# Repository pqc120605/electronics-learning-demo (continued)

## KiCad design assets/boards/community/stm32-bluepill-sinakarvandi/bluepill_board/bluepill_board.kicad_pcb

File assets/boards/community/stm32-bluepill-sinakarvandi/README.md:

# PCB Designs

My random PCB designs using [KiCad](https://www.kicad.org/).

- **Blue Pill Board**

  Custom PCB design for STM32 "Blue Pill" development board.

- **ESP32-S3 Board**

  Schematic and layout for ESP32-S3-based design.

- **ESP32 WROOM Board**

  PCB based on ESP32-WROOM module.

- **LED Blinker**

  Simple circuit for testing LEDs and basic PCB workflow.

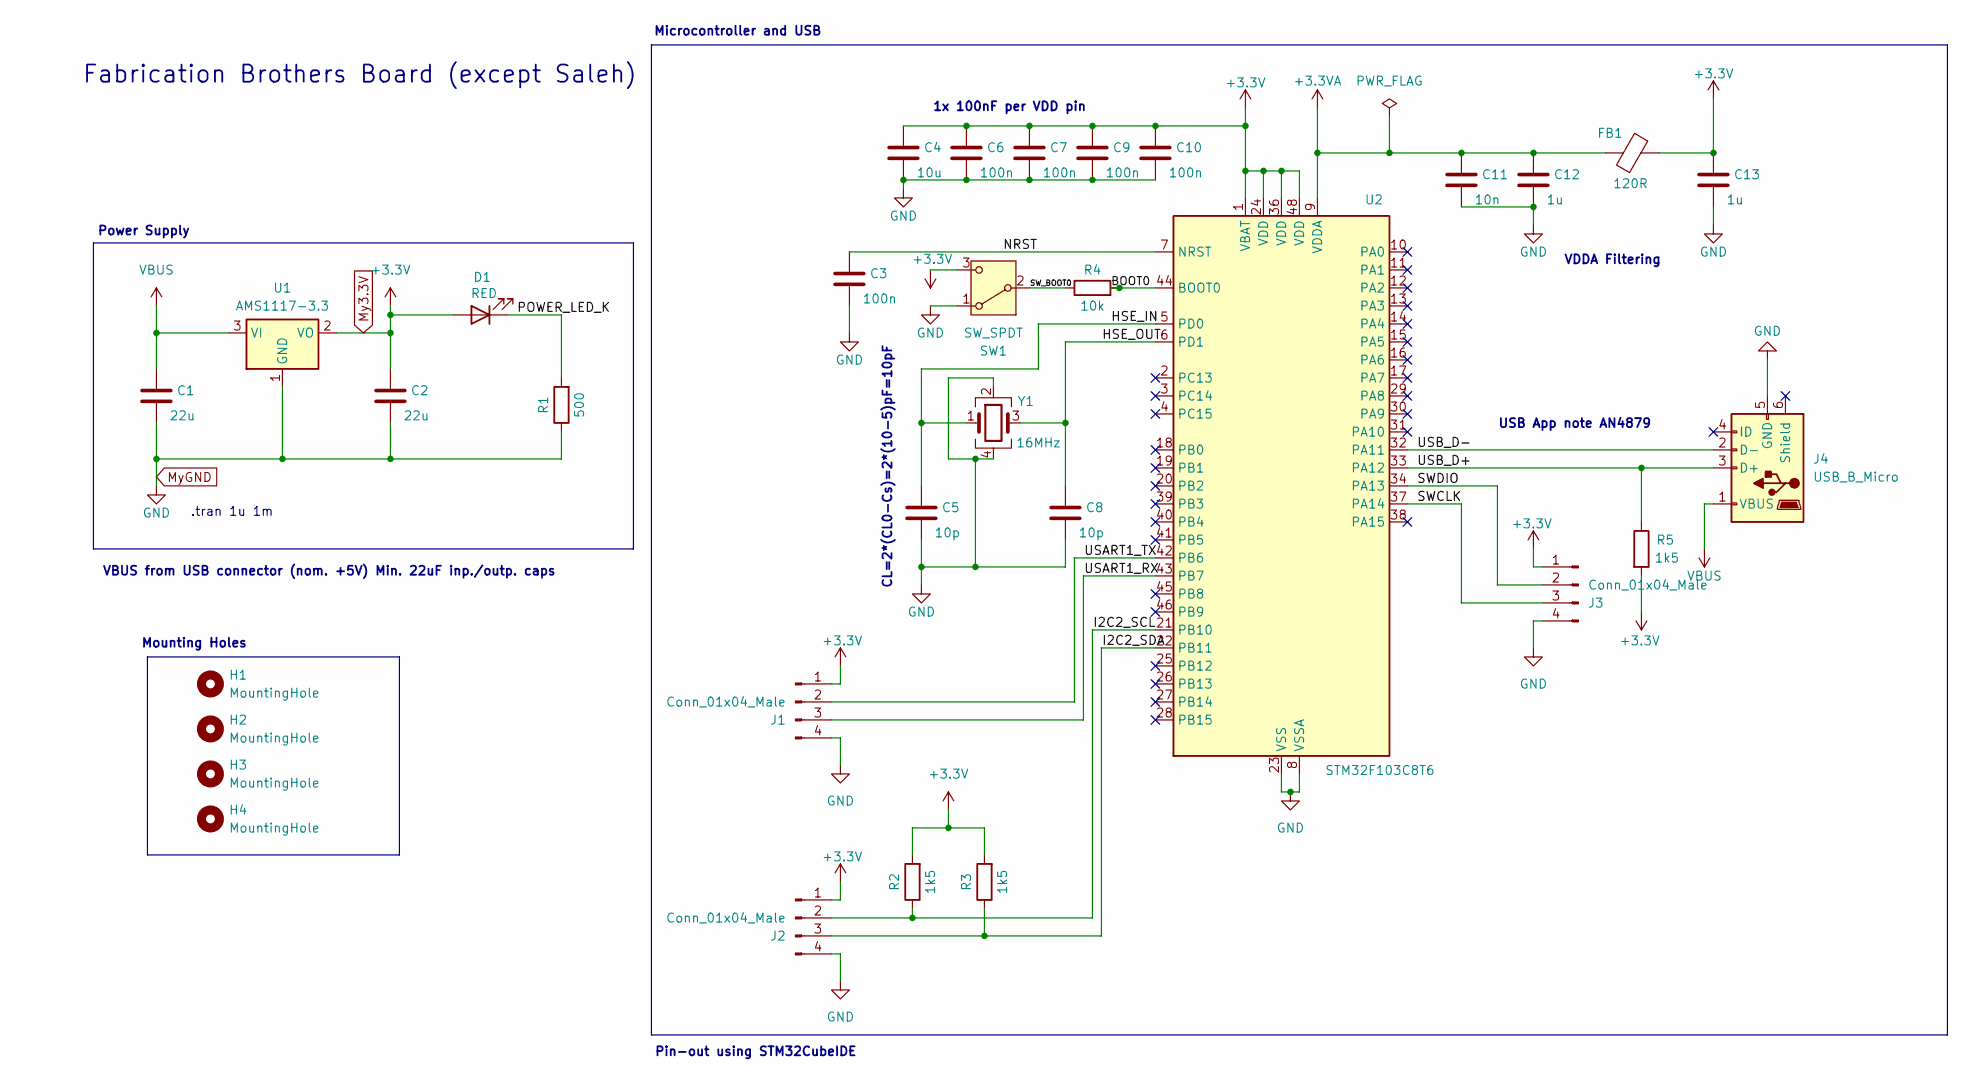
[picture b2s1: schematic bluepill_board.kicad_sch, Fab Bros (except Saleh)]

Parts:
C1, C2: 22u; C_0805_2012Metric; LCSC C296720
C3, C6, C7, C9, C10: 100n; C_0402_1005Metric; LCSC C1525
C4: 10u; C_0603_1608Metric; LCSC C19702
C5, C8: 10p; C_0402_1005Metric; LCSC C32949
C11: 10n; C_0402_1005Metric; LCSC C15195
C12, C13: 1u; C_0402_1005Metric; LCSC C29266
D1: RED; LED_0603_1608Metric; LCSC C7371906
FB1: 120R; L_0603_1608Metric; LCSC C14709
H1, H2, H3, H4: MountingHole; MountingHole_2.2mm_M2
J1, J2, J3: Conn_01x04_Male; PinHeader_1x04_P2.54mm_Vertical; LCSC C2337
J4: USB_B_Micro; USB_Micro-B_Wuerth_629105150521; LCSC C2894326
R1: 500; R_0402_1005Metric; LCSC C25109
R2, R3, R5: 1k5; R_0402_1005Metric; LCSC C25867
R4: 10k; R_0402_1005Metric; LCSC C25744
SW1: SW_SPDT; SW_SPDT_PCM12; LCSC C221841
U1: AMS1117-3.3; SOT-223-3_TabPin2; LCSC C6186
U2: STM32F103C8T6; LQFP-48_7x7mm_P0.5mm; LCSC C8734
Y1: 16MHz; Crystal_SMD_3225-4Pin_3.2x2.5mm; LCSC C518160

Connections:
+3.3V: C2.1, C4.1, C6.1, C7.1, C9.1, C10.1, C13.1, D1.2 (A), FB1.2, J1.1, J2.1, J3.1, R2.2, R3.2, R5.2, SW1.3 (C), U1.2 (VO), U2.1 (VBAT), U2.24 (VDD), U2.36 (VDD), U2.48 (VDD)
+3.3VA: C11.1, C12.1, FB1.1, U2.9 (VDDA)
/BOOT0: R4.2, U2.44 (BOOT0)
/HSE_IN: C5.1, U2.5 (PD0), Y1.1
/HSE_OUT: C8.1, U2.6 (PD1), Y1.3
/I2C2_SCL: J2.2, R2.1, U2.21 (PB10)
/I2C2_SDA: J2.3, R3.1, U2.22 (PB11)
/NRST: C3.1, U2.7 (NRST)
/POWER_LED_K: D1.1 (K), R1.2
/SWCLK: J3.3, U2.37 (PA14)
/SWDIO: J3.2, U2.34 (PA13)
/SW_BOOT0: R4.1, SW1.2 (B)
/USART1_RX: J1.3, U2.43 (PB7)
/USART1_TX: J1.2, U2.42 (PB6)
/USB_D+: J4.3 (D+), R5.1, U2.33 (PA12)
/USB_D-: J4.2 (D-), U2.32 (PA11)
GND: C1.2, C2.2, C3.2, C4.2, C5.2, C6.2, C7.2, C8.2, C9.2, C10.2, C11.2, C12.2, C13.2, J1.4, J2.4, J3.4, J4.5 (GND), R1.1, SW1.1 (A), U1.1 (GND), U2.8 (VSSA), U2.23 (VSS), U2.35 (VSS), U2.47 (VSS), Y1.2, Y1.4
VBUS: C1.1, J4.1 (VBUS), U1.3 (VI)

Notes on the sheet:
CL=2*(CL0-Cs)=2*(10-5)pF=10pF
Pin-out using STM32CubeIDE
Mounting Holes
VBUS from USB connector (nom. +5V) Min. 22uF inp./outp. caps
Fabrication Brothers Board (except Saleh)
Power Supply
VDDA Filtering
1x 100nF per VDD pin
USB App note AN4879
Microcontroller and USB
.tran 1u 1m

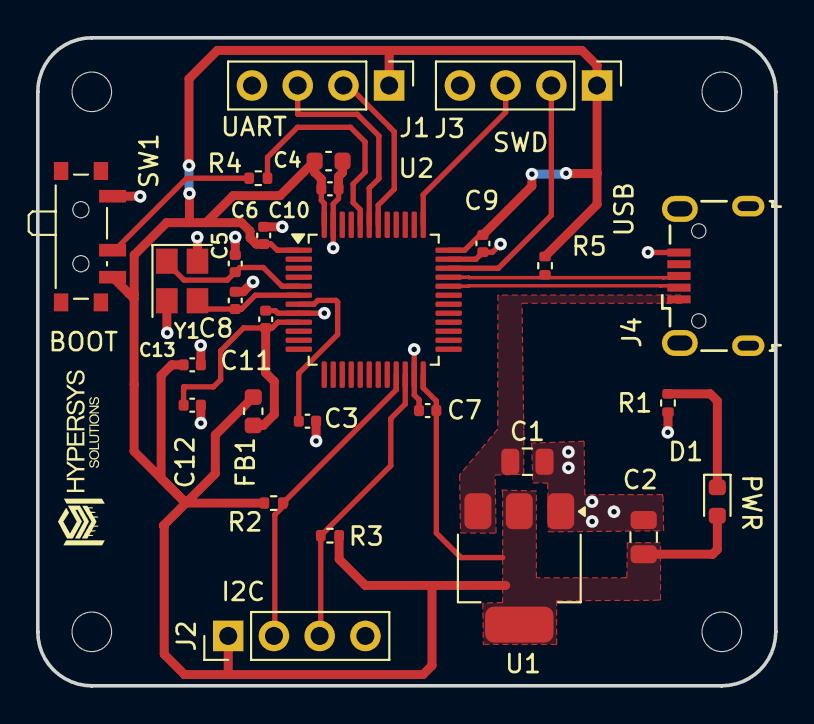
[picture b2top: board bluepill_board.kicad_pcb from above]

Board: 2 copper layers, 41.0 x 36.0 mm, 32 parts (0 on the bottom side), 18 nets.

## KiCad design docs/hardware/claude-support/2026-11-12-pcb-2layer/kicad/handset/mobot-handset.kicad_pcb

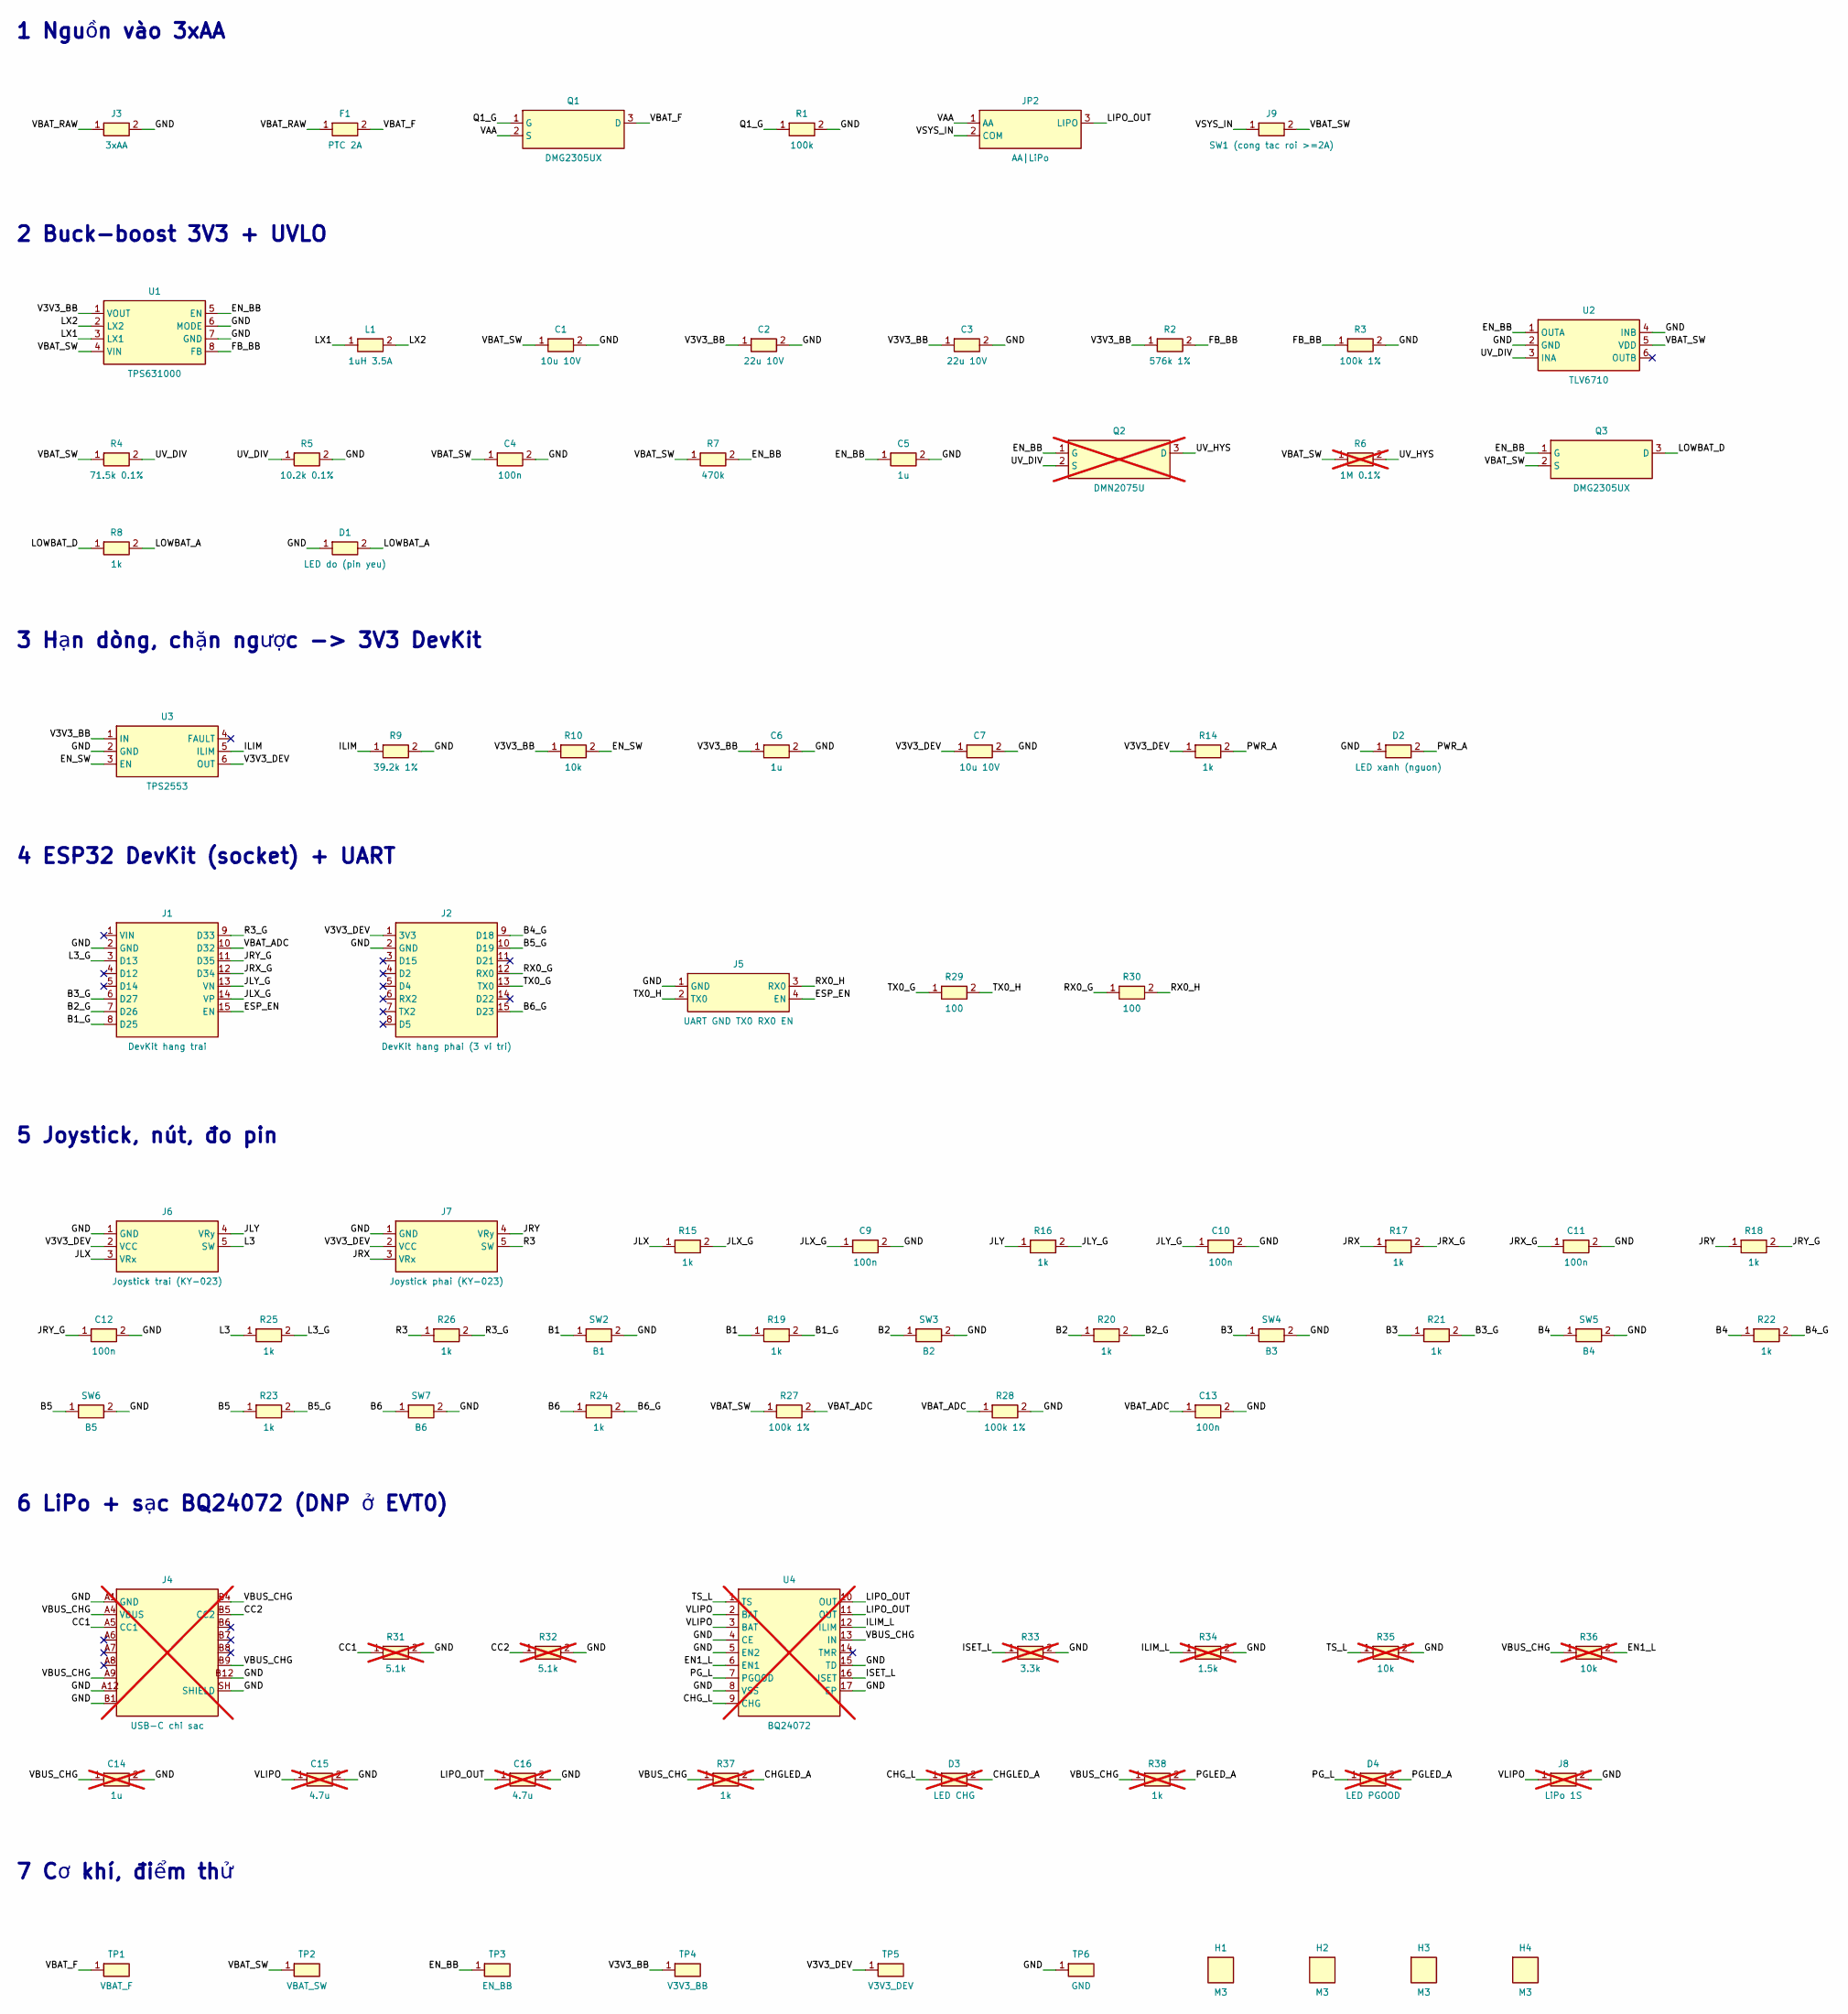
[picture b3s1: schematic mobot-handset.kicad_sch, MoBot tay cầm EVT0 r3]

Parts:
C1, C7: 10u 10V; C_0805_2012Metric
C2, C3: 22u 10V; C_0805_2012Metric
C4, C9, C10, C11, C12, C13: 100n; C_0603_1608Metric
C5, C6: 1u; C_0603_1608Metric
C14: 1u; C_0603_1608Metric; not fitted
C15, C16: 4.7u; C_0603_1608Metric; not fitted
D1: LED do (pin yeu); LED_0603_1608Metric
D2: LED xanh (nguon); LED_0603_1608Metric
D3: LED CHG; LED_0603_1608Metric; not fitted
D4: LED PGOOD; LED_0603_1608Metric; not fitted
F1: PTC 2A; Fuse_1812_4532Metric; MPN MF-MSMF200/8X
H1, H2, H3, H4: M3; MountingHole_3.2mm_M3
J1: DevKit hang trai; PinSocket_1x15_P2.54mm_Vertical
J2: DevKit hang phai (3 vi tri); PinSocket_1x15_Alt3Rows_22.86_25.40_27.94
J3: 3xAA; JST_XH_B2B-XH-A_1x02_P2.50mm_Vertical; MPN B2B-XH-A
J4: USB-C chi sac; USB_C_Receptacle_GCT_USB4105-xx-A_16P_TopMnt_Horizontal; MPN USB4105-GF-A; not fitted
J5: UART GND TX0 RX0 EN; PinHeader_1x04_P2.54mm_Vertical
J6: Joystick trai (KY-023); PinHeader_1x05_P2.54mm_Vertical
J7: Joystick phai (KY-023); PinHeader_1x05_P2.54mm_Vertical
J8: LiPo 1S; JST_PH_B2B-PH-K_1x02_P2.00mm_Vertical; MPN B2B-PH-K-S; not fitted
J9: SW1 (cong tac roi >=2A); JST_XH_B2B-XH-A_1x02_P2.50mm_Vertical; MPN B2B-XH-A
JP2: AA|LiPo; SolderJumper-3_P1.3mm_Bridged12_RoundedPad1.0x1.5mm
L1: 1uH 3.5A; L_Changjiang_FNR4030S; MPN XEL4030-102ME
Q1, Q3: DMG2305UX; SOT-23; MPN DMG2305UX-7
Q2: DMN2075U; SOT-23; MPN DMN2075U-7; not fitted
R1: 100k; R_0603_1608Metric
R2: 576k 1%; R_0603_1608Metric
R3, R27, R28: 100k 1%; R_0603_1608Metric
R4: 71.5k 0.1%; R_0603_1608Metric
R5: 10.2k 0.1%; R_0603_1608Metric
R6: 1M 0.1%; R_0603_1608Metric; not fitted
R7: 470k; R_0603_1608Metric
R8, R14, R15, R16, R17, R18, R19, R20, R21, R22, R23, R24, R25, R26: 1k; R_0603_1608Metric
R9: 39.2k 1%; R_0603_1608Metric
R10: 10k; R_0603_1608Metric
R29, R30: 100; R_0603_1608Metric
R31, R32: 5.1k; R_0603_1608Metric; not fitted
R33: 3.3k; R_0603_1608Metric; not fitted
R34: 1.5k; R_0603_1608Metric; not fitted
R35, R36: 10k; R_0603_1608Metric; not fitted
R37, R38: 1k; R_0603_1608Metric; not fitted
SW2: B1; SW_PUSH_6mm
SW3: B2; SW_PUSH_6mm
SW4: B3; SW_PUSH_6mm
SW5: B4; SW_PUSH_6mm
SW6: B5; SW_PUSH_6mm
SW7: B6; SW_PUSH_6mm
TP1: VBAT_F; TestPoint_Pad_D1.5mm
TP2: VBAT_SW; TestPoint_Pad_D1.5mm
TP3: EN_BB; TestPoint_Pad_D1.5mm
TP4: V3V3_BB; TestPoint_Pad_D1.5mm
TP5: V3V3_DEV; TestPoint_Pad_D1.5mm
TP6: GND; TestPoint_Pad_D1.5mm
U1: TPS631000; SOT-583-8; MPN TPS631000DRLR
U2: TLV6710; TSOT-23-6; MPN TLV6710DDCR
U3: TPS2553; SOT-23-6; MPN TPS2553DBVR
U4: BQ24072; VQFN-16-1EP_3x3mm_P0.5mm_EP1.68x1.68mm; MPN BQ24072RGTR; not fitted

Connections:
/B1: R19.1, SW2.1
/B1_G: J1.8 (D25), R19.2
/B2: R20.1, SW3.1
/B2_G: J1.7 (D26), R20.2
/B3: R21.1, SW4.1
/B3_G: J1.6 (D27), R21.2
/B4: R22.1, SW5.1
/B4_G: J2.9 (D18), R22.2
/B5: R23.1, SW6.1
/B5_G: J2.10 (D19), R23.2
/B6: R24.1, SW7.1
/B6_G: J2.15 (D23), R24.2
/CC1: J4.A5 (CC1), R31.1
/CC2: J4.B5 (CC2), R32.1
/CHGLED_A: D3.2 (A), R37.2
/CHG_L: D3.1 (K), U4.9 (CHG)
/EN1_L: R36.2, U4.6 (EN1)
/EN_BB: C5.1, Q2.1 (G), Q3.1 (G), R7.2, TP3.1, U1.5 (EN), U2.1 (OUTA)
/EN_SW: R10.2, U3.3 (EN)
/ESP_EN: J1.15 (EN), J5.4 (EN)
/FB_BB: R2.2, R3.1, U1.8 (FB)
/GND: C1.2, C2.2, C3.2, C4.2, C5.2, C6.2, C7.2, C9.2, C10.2, C11.2, C12.2, C13.2, C14.2, C15.2, C16.2, D1.1 (K), D2.1 (K), J1.2 (GND), J2.2 (GND), J3.2 (-), J4.A1 (GND), J4.A12, J4.B1, J4.B12, J4.SH (SHIELD), J5.1 (GND), J6.1 (GND), J7.1 (GND), J8.2 (-), R1.2, R3.2, R5.2, R9.2, R28.2, R31.2, R32.2, R33.2, R34.2, R35.2, SW2.2, SW3.2, SW4.2, SW5.2, SW6.2, SW7.2, TP6.1, U1.6 (MODE), U1.7 (GND), U2.2 (GND), U2.4 (INB), U3.2 (GND), U4.4 (CE), U4.5 (EN2), U4.8 (VSS), U4.15 (TD), U4.17 (EP)
/ILIM: R9.1, U3.5 (ILIM)
/ILIM_L: R34.1, U4.12 (ILIM)
/ISET_L: R33.1, U4.16 (ISET)
/JLX: J6.3 (VRx), R15.1
/JLX_G: C9.1, J1.14 (VP), R15.2
/JLY: J6.4 (VRy), R16.1
/JLY_G: C10.1, J1.13 (VN), R16.2
/JRX: J7.3 (VRx), R17.1
/JRX_G: C11.1, J1.12 (D34), R17.2
/JRY: J7.4 (VRy), R18.1
/JRY_G: C12.1, J1.11 (D35), R18.2
/L3: J6.5 (SW), R25.1
/L3_G: J1.3 (D13), R25.2
/LIPO_OUT: C16.1, JP2.3 (LIPO), U4.10 (OUT), U4.11 (OUT)
/LOWBAT_A: D1.2 (A), R8.2
/LOWBAT_D: Q3.3 (D), R8.1
/LX1: L1.1, U1.3 (LX1)
/LX2: L1.2, U1.2 (LX2)
/PGLED_A: D4.2 (A), R38.2
/PG_L: D4.1 (K), U4.7 (PGOOD)
/PWR_A: D2.2 (A), R14.2
/Q1_G: Q1.1 (G), R1.1
/R3: J7.5 (SW), R26.1
/R3_G: J1.9 (D33), R26.2
/RX0_G: J2.12 (RX0), R30.1
/RX0_H: J5.3 (RX0), R30.2
/TS_L: R35.1, U4.1 (TS)
/TX0_G: J2.13 (TX0), R29.1
/TX0_H: J5.2 (TX0), R29.2
/UV_DIV: Q2.2 (S), R4.2, R5.1, U2.3 (INA)
/UV_HYS: Q2.3 (D), R6.2
/V3V3_BB: C2.1, C3.1, C6.1, R2.1, R10.1, TP4.1, U1.1 (VOUT), U3.1 (IN)
/V3V3_DEV: C7.1, J2.1 (3V3), J6.2 (VCC), J7.2 (VCC), R14.1, TP5.1, U3.6 (OUT)
/VAA: JP2.1 (AA), Q1.2 (S)
/VBAT_ADC: C13.1, J1.10 (D32), R27.2, R28.1
/VBAT_F: F1.2, Q1.3 (D), TP1.1
/VBAT_RAW: F1.1, J3.1 (+)
/VBAT_SW: C1.1, C4.1, J9.2 (OUT), Q3.2 (S), R4.1, R6.1, R7.1, R27.1, TP2.1, U1.4 (VIN), U2.5 (VDD)
/VBUS_CHG: C14.1, J4.A4 (VBUS), J4.A9, J4.B4, J4.B9, R36.1, R37.1, R38.1, U4.13 (IN)
/VLIPO: C15.1, J8.1 (+), U4.2 (BAT), U4.3 (BAT)
/VSYS_IN: J9.1 (IN), JP2.2 (COM)

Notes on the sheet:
1 Nguồn vào 3xAA
2 Buck-boost 3V3 + UVLO
3 Hạn dòng, chặn ngược -> 3V3 DevKit
4 ESP32 DevKit (socket) + UART
5 Joystick, nút, đo pin
6 LiPo + sạc BQ24072 (DNP ở EVT0)
7 Cơ khí, điểm thử

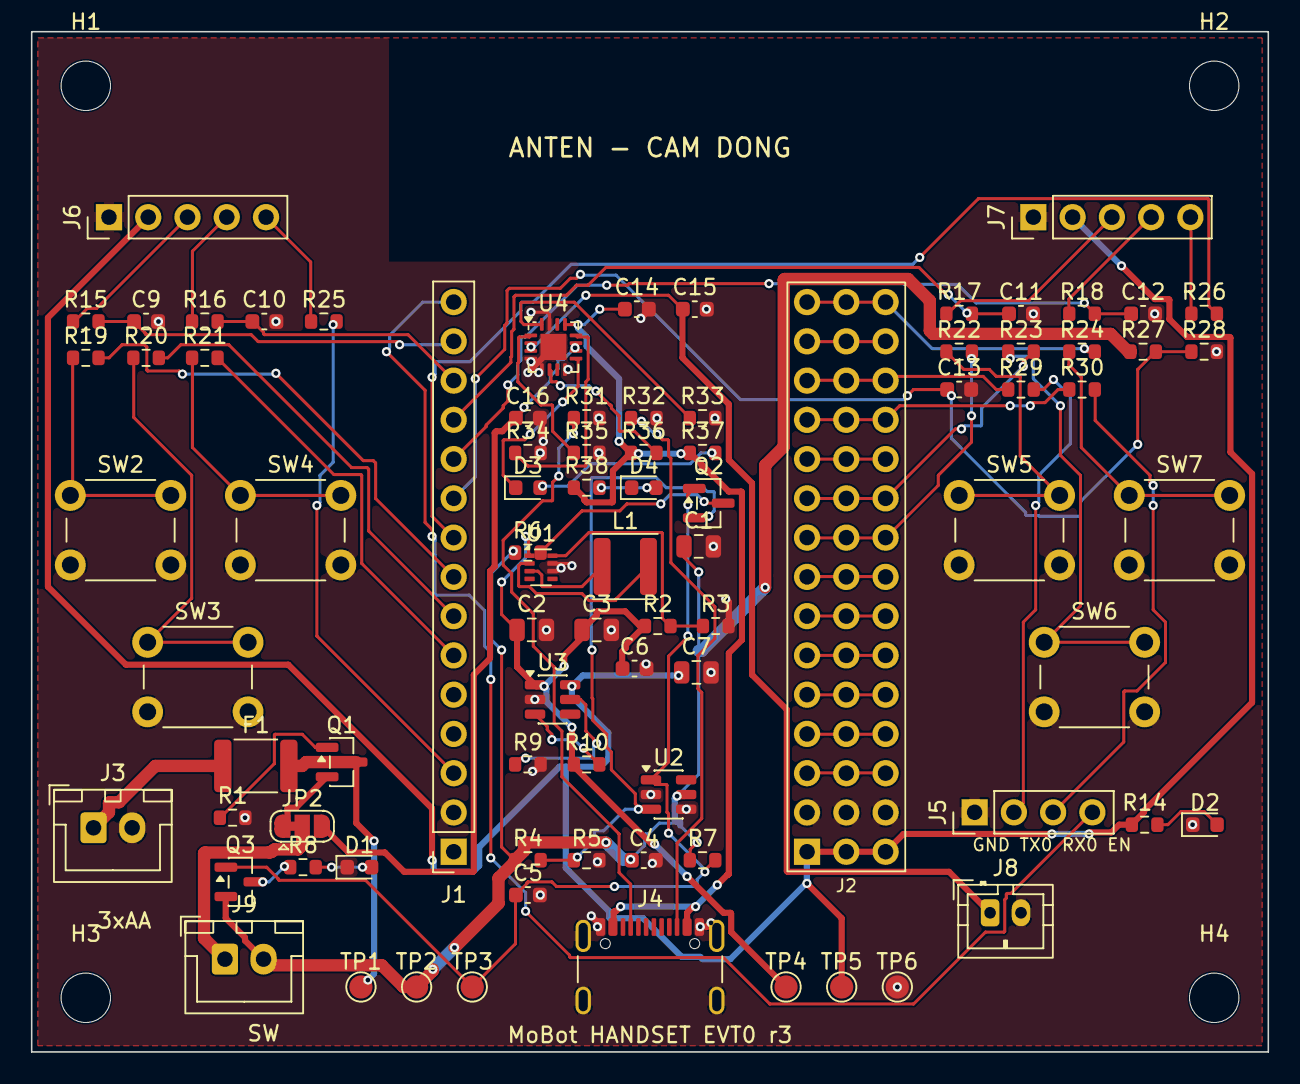
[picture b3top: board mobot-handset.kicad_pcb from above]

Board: 2 copper layers, 80.0 x 66.0 mm, 89 parts (0 on the bottom side), 63 nets.

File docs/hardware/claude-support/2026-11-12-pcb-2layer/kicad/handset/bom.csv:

"Ref","Value","Footprint","MPN","Qty","DNP"
"C1,C7","10u 10V","Capacitor_SMD:C_0805_2012Metric","","2",""
"C2,C3","22u 10V","Capacitor_SMD:C_0805_2012Metric","","2",""
"C4,C9-C13","100n","Capacitor_SMD:C_0603_1608Metric","","6",""
"C5,C6","1u","Capacitor_SMD:C_0603_1608Metric","","2",""
"C14","1u","Capacitor_SMD:C_0603_1608Metric","","1","DNP"
"C15,C16","4.7u","Capacitor_SMD:C_0603_1608Metric","","2","DNP"
"D1","LED do (pin yeu)","LED_SMD:LED_0603_1608Metric","","1",""
"D2","LED xanh (nguon)","LED_SMD:LED_0603_1608Metric","","1",""
"D3","LED CHG","LED_SMD:LED_0603_1608Metric","","1","DNP"
"D4","LED PGOOD","LED_SMD:LED_0603_1608Metric","","1","DNP"
"F1","PTC 2A","Fuse:Fuse_1812_4532Metric","MF-MSMF200/8X","1",""
"J1","DevKit hang trai","Connector_PinSocket_2.54mm:PinSocket_1x15_P2.54mm_Vertical","","1",""
"J2","DevKit hang phai (3 vi tri)","mobot:PinSocket_1x15_Alt3Rows_22.86_25.40_27.94","","1",""
"J3","3xAA","Connector_JST:JST_XH_B2B-XH-A_1x02_P2.50mm_Vertical","B2B-XH-A","1",""
"J4","USB-C chi sac","Connector_USB:USB_C_Receptacle_GCT_USB4105-xx-A_16P_TopMnt_Horizontal","USB4105-GF-A","1","DNP"
"J5","UART GND TX0 RX0 EN","Connector_PinHeader_2.54mm:PinHeader_1x04_P2.54mm_Vertical","","1",""
"J6","Joystick trai (KY-023)","Connector_PinHeader_2.54mm:PinHeader_1x05_P2.54mm_Vertical","","1",""
"J7","Joystick phai (KY-023)","Connector_PinHeader_2.54mm:PinHeader_1x05_P2.54mm_Vertical","","1",""
"J8","LiPo 1S","Connector_JST:JST_PH_B2B-PH-K_1x02_P2.00mm_Vertical","B2B-PH-K-S","1","DNP"
"J9","SW1 (cong tac roi >=2A)","Connector_JST:JST_XH_B2B-XH-A_1x02_P2.50mm_Vertical","B2B-XH-A","1",""
"L1","1uH 3.5A","Inductor_SMD:L_Changjiang_FNR4030S","XEL4030-102ME","1",""
"Q1,Q3","DMG2305UX","Package_TO_SOT_SMD:SOT-23","DMG2305UX-7","2",""
"Q2","DMN2075U","Package_TO_SOT_SMD:SOT-23","DMN2075U-7","1","DNP"
"R1","100k","Resistor_SMD:R_0603_1608Metric","","1",""
"R2","576k 1%","Resistor_SMD:R_0603_1608Metric","","1",""
"R3,R27,R28","100k 1%","Resistor_SMD:R_0603_1608Metric","","3",""
"R4","71.5k 0.1%","Resistor_SMD:R_0603_1608Metric","","1",""
"R5","10.2k 0.1%","Resistor_SMD:R_0603_1608Metric","","1",""
"R6","1M 0.1%","Resistor_SMD:R_0603_1608Metric","","1","DNP"
"R7","470k","Resistor_SMD:R_0603_1608Metric","","1",""
"R8,R14-R26","1k","Resistor_SMD:R_0603_1608Metric","","14",""
"R9","39.2k 1%","Resistor_SMD:R_0603_1608Metric","","1",""
"R10","10k","Resistor_SMD:R_0603_1608Metric","","1",""
"R29,R30","100","Resistor_SMD:R_0603_1608Metric","","2",""
"R31,R32","5.1k","Resistor_SMD:R_0603_1608Metric","","2","DNP"
"R33","3.3k","Resistor_SMD:R_0603_1608Metric","","1","DNP"
"R34","1.5k","Resistor_SMD:R_0603_1608Metric","","1","DNP"
"R35,R36","10k","Resistor_SMD:R_0603_1608Metric","","2","DNP"
"R37,R38","1k","Resistor_SMD:R_0603_1608Metric","","2","DNP"
"SW2","B1","Button_Switch_THT:SW_PUSH_6mm","","1",""
"SW3","B2","Button_Switch_THT:SW_PUSH_6mm","","1",""
"SW4","B3","Button_Switch_THT:SW_PUSH_6mm","","1",""
"SW5","B4","Button_Switch_THT:SW_PUSH_6mm","","1",""
"SW6","B5","Button_Switch_THT:SW_PUSH_6mm","","1",""
"SW7","B6","Button_Switch_THT:SW_PUSH_6mm","","1",""
"U1","TPS631000","Package_TO_SOT_SMD:SOT-583-8","TPS631000DRLR","1",""
"U2","TLV6710","Package_TO_SOT_SMD:TSOT-23-6","TLV6710DDCR","1",""
"U3","TPS2553","Package_TO_SOT_SMD:SOT-23-6","TPS2553DBVR","1",""
"U4","BQ24072","Package_DFN_QFN:VQFN-16-1EP_3x3mm_P0.5mm_EP1.68x1.68mm","BQ24072RGTR","1","DNP"

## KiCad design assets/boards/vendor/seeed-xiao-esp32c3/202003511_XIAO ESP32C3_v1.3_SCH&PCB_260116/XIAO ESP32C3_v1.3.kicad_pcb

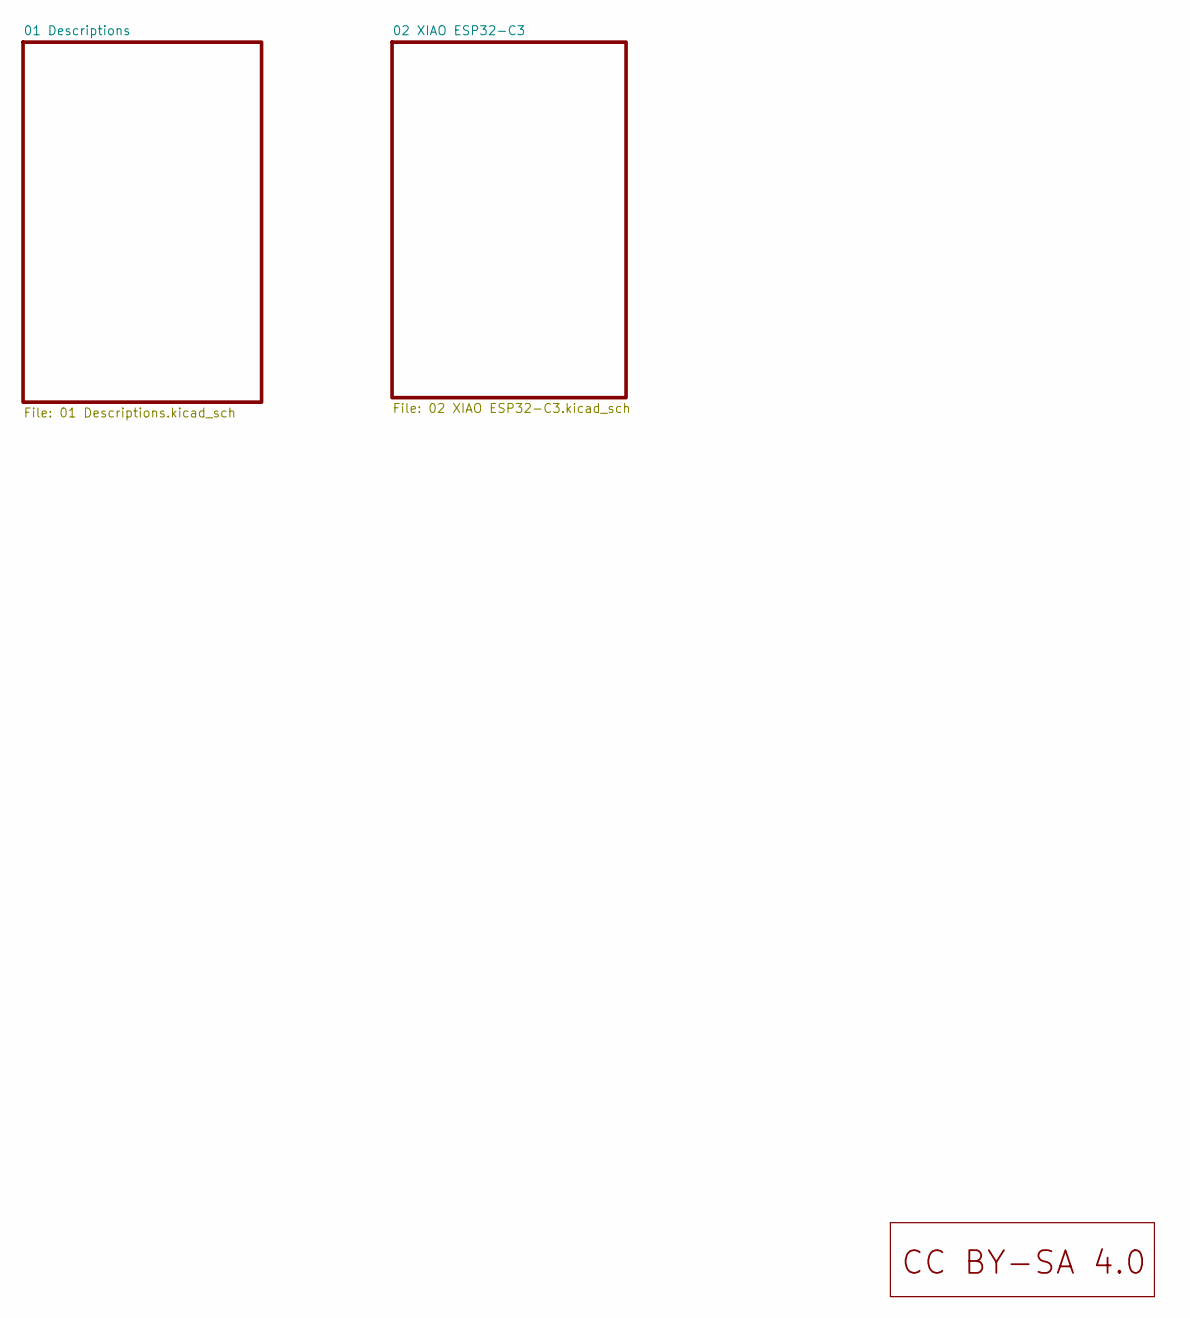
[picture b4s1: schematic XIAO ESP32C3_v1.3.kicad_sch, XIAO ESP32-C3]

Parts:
U3: LOGO_CC_BY-SA_4.0

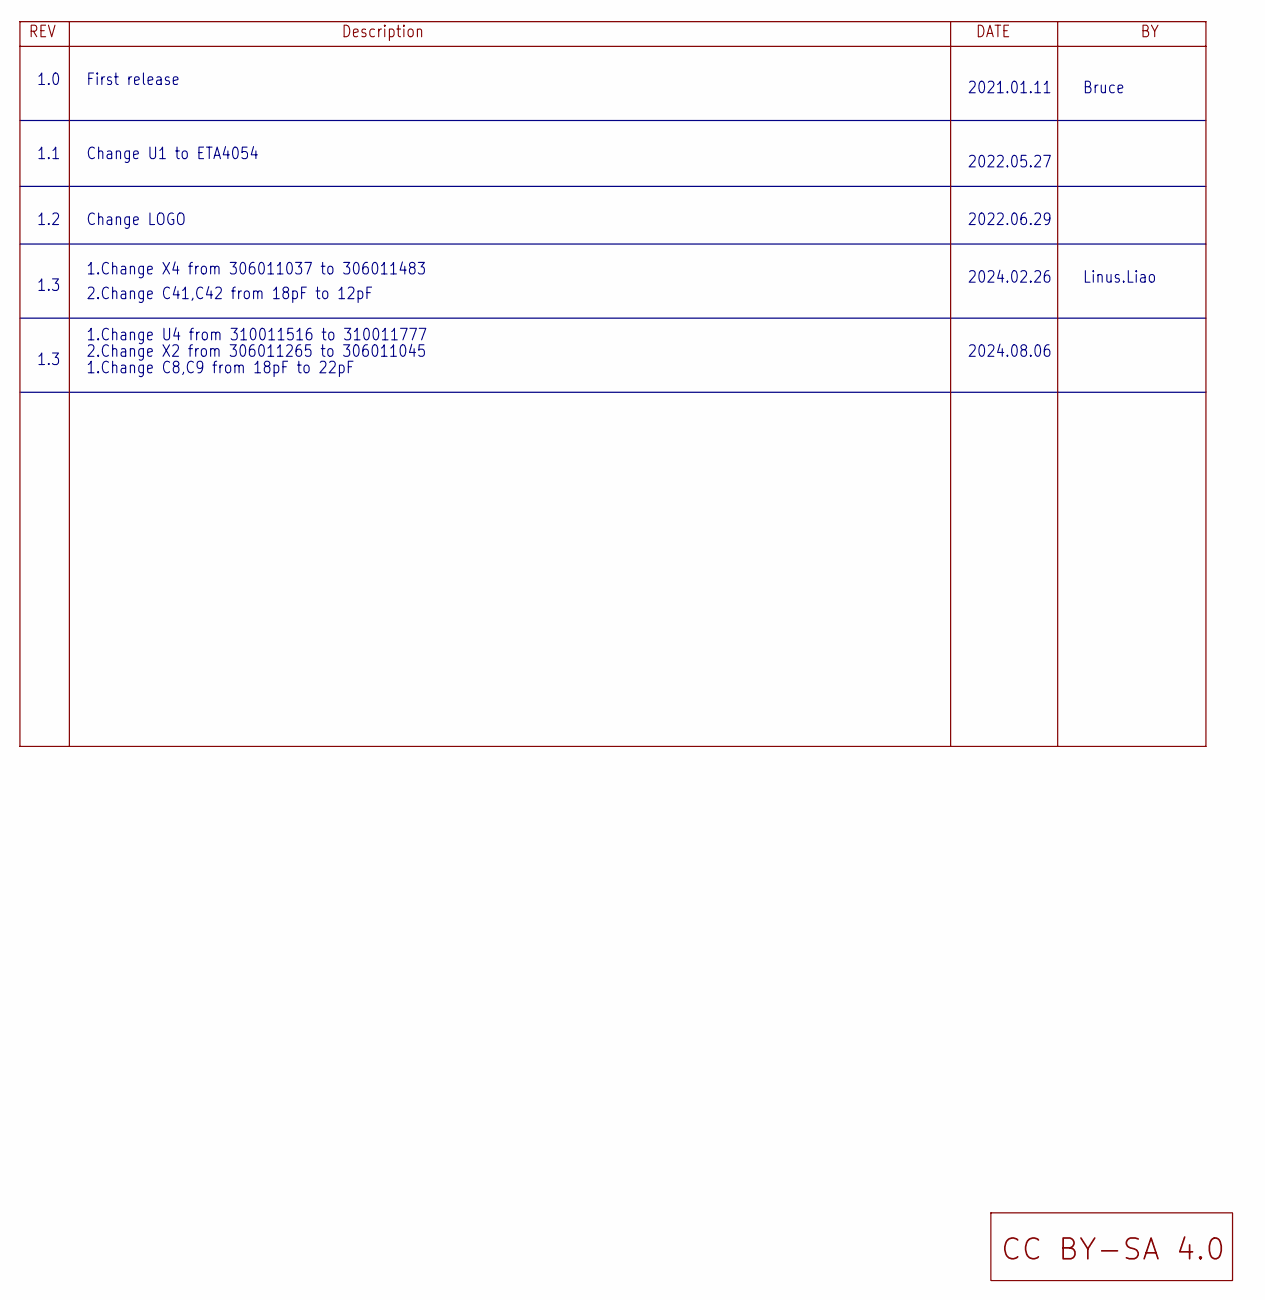
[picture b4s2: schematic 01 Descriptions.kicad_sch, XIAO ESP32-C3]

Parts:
U5: LOGO_CC_BY-SA_4.0

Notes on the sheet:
1.0
1.Change X4 from 306011037 to 306011483
1.Change U4 from 310011516 to 310011777
1.3
1.2
2.Change C41,C42 from 18pF to 12pF
2022.06.29
2022.05.27
Linus.Liao
2.Change X2 from 306011265 to 306011045
Bruce
2024.08.06
1.1
Change LOGO
2024.02.26
2021.01.11
First release
Change U1 to ETA4054
1.Change C8,C9 from 18pF to 22pF
